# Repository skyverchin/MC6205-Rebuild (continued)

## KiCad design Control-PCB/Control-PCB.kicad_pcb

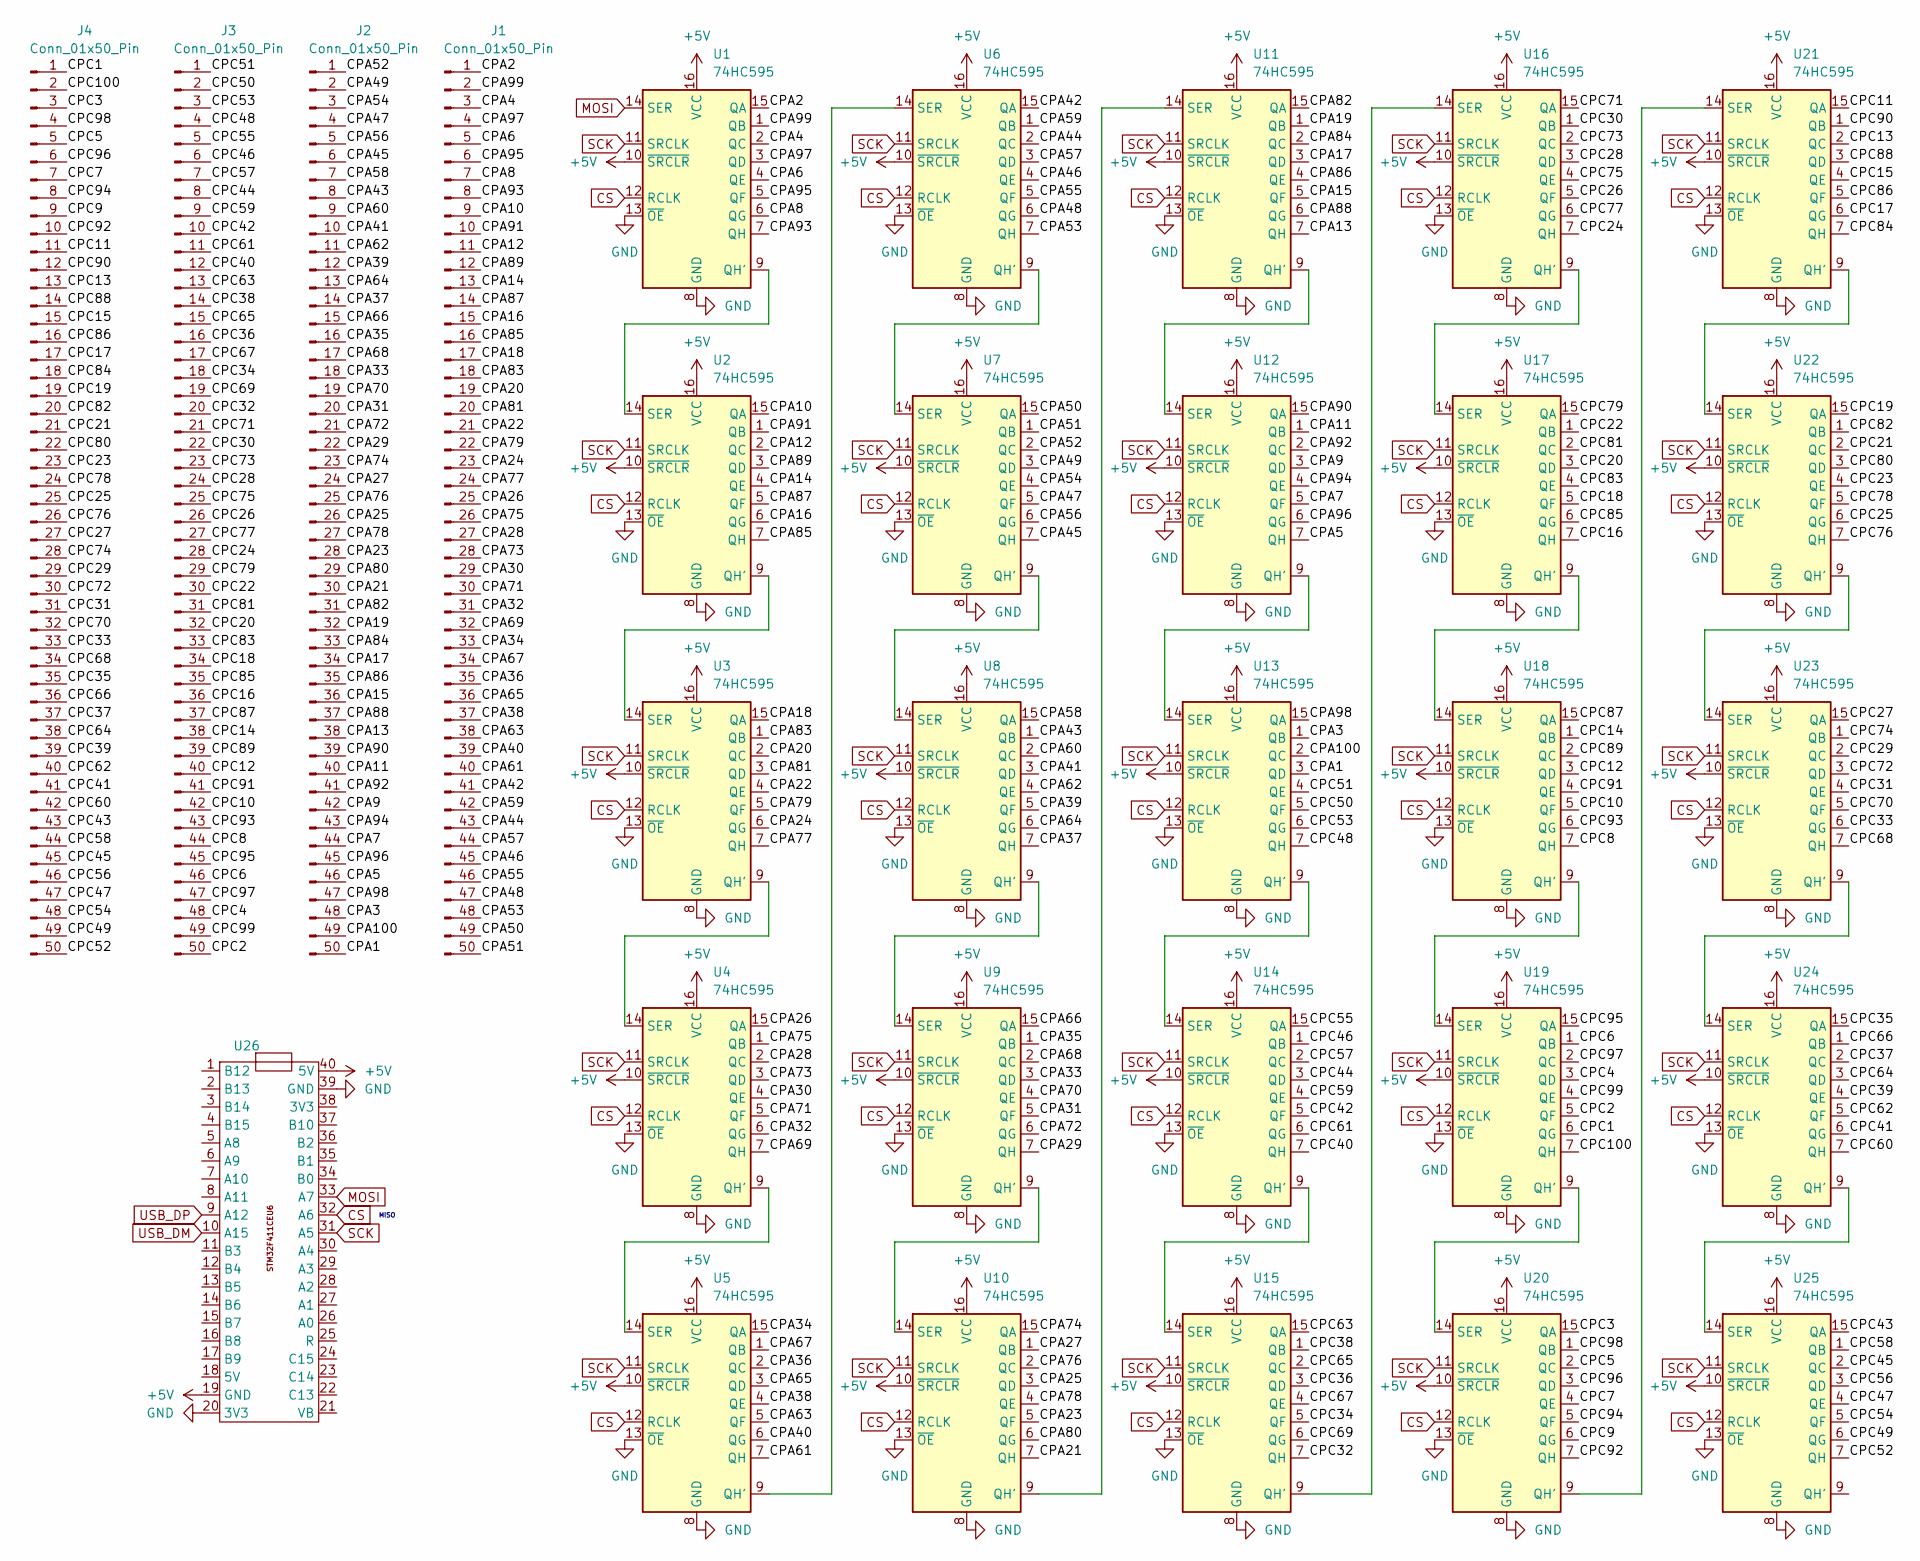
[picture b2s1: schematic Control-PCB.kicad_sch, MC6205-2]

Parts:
J1, J2, J3, J4: Conn_01x50_Pin; Molex_54132-5033_1x50-1MP_P0.5mm_Horizontal
U1, U2, U3, U4, U5, U6, U7, U8, U9, U10, U11, U12, U13, U14, U15, U16, U17, U18, U19, U20, U21, U22, U23, U24, U25: 74HC595; CERDIP-16_W7.62mm_SideBrazed
U26: DIP-40_W15.24mm

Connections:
+5V: U1.10 (~SRCLR), U1.16 (VCC), U2.10 (~SRCLR), U2.16 (VCC), U3.10 (~SRCLR), U3.16 (VCC), U4.10 (~SRCLR), U4.16 (VCC), U5.10 (~SRCLR), U5.16 (VCC), U6.10 (~SRCLR), U6.16 (VCC), U7.10 (~SRCLR), U7.16 (VCC), U8.10 (~SRCLR), U8.16 (VCC), U9.10 (~SRCLR), U9.16 (VCC), U10.10 (~SRCLR), U10.16 (VCC), U11.10 (~SRCLR), U11.16 (VCC), U12.10 (~SRCLR), U12.16 (VCC), U13.10 (~SRCLR), U13.16 (VCC), U14.10 (~SRCLR), U14.16 (VCC), U15.10 (~SRCLR), U15.16 (VCC), U16.10 (~SRCLR), U16.16 (VCC), U17.10 (~SRCLR), U17.16 (VCC), U18.10 (~SRCLR), U18.16 (VCC), U19.10 (~SRCLR), U19.16 (VCC), U20.10 (~SRCLR), U20.16 (VCC), U21.10 (~SRCLR), U21.16 (VCC), U22.10 (~SRCLR), U22.16 (VCC), U23.10 (~SRCLR), U23.16 (VCC), U24.10 (~SRCLR), U24.16 (VCC), U25.10 (~SRCLR), U25.16 (VCC), U26.19 (GND), U26.40 (5V)
/CPA1: J2.50, U13.3 (QD)
/CPA2: J1.1, U1.15 (QA)
/CPA3: J2.48, U13.1 (QB)
/CPA4: J1.3, U1.2 (QC)
/CPA5: J2.46, U12.7 (QH)
/CPA6: J1.5, U1.4 (QE)
/CPA7: J2.44, U12.5 (QF)
/CPA8: J1.7, U1.6 (QG)
/CPA9: J2.42, U12.3 (QD)
/CPA10: J1.9, U2.15 (QA)
/CPA11: J2.40, U12.1 (QB)
/CPA12: J1.11, U2.2 (QC)
/CPA13: J2.38, U11.7 (QH)
/CPA14: J1.13, U2.4 (QE)
/CPA15: J2.36, U11.5 (QF)
/CPA16: J1.15, U2.6 (QG)
/CPA17: J2.34, U11.3 (QD)
/CPA18: J1.17, U3.15 (QA)
/CPA19: J2.32, U11.1 (QB)
/CPA20: J1.19, U3.2 (QC)
/CPA21: J2.30, U10.7 (QH)
/CPA22: J1.21, U3.4 (QE)
/CPA23: J2.28, U10.5 (QF)
/CPA24: J1.23, U3.6 (QG)
/CPA25: J2.26, U10.3 (QD)
/CPA26: J1.25, U4.15 (QA)
/CPA27: J2.24, U10.1 (QB)
/CPA28: J1.27, U4.2 (QC)
/CPA29: J2.22, U9.7 (QH)
/CPA30: J1.29, U4.4 (QE)
/CPA31: J2.20, U9.5 (QF)
/CPA32: J1.31, U4.6 (QG)
/CPA33: J2.18, U9.3 (QD)
/CPA34: J1.33, U5.15 (QA)
/CPA35: J2.16, U9.1 (QB)
/CPA36: J1.35, U5.2 (QC)
/CPA37: J2.14, U8.7 (QH)
/CPA38: J1.37, U5.4 (QE)
/CPA39: J2.12, U8.5 (QF)
/CPA40: J1.39, U5.6 (QG)
/CPA41: J2.10, U8.3 (QD)
/CPA42: J1.41, U6.15 (QA)
/CPA43: J2.8, U8.1 (QB)
/CPA44: J1.43, U6.2 (QC)
/CPA45: J2.6, U7.7 (QH)
/CPA46: J1.45, U6.4 (QE)
/CPA47: J2.4, U7.5 (QF)
/CPA48: J1.47, U6.6 (QG)
/CPA49: J2.2, U7.3 (QD)
/CPA50: J1.49, U7.15 (QA)
/CPA51: J1.50, U7.1 (QB)
/CPA52: J2.1, U7.2 (QC)
/CPA53: J1.48, U6.7 (QH)
/CPA54: J2.3, U7.4 (QE)
/CPA55: J1.46, U6.5 (QF)
/CPA56: J2.5, U7.6 (QG)
/CPA57: J1.44, U6.3 (QD)
/CPA58: J2.7, U8.15 (QA)
/CPA59: J1.42, U6.1 (QB)
/CPA60: J2.9, U8.2 (QC)
/CPA61: J1.40, U5.7 (QH)
/CPA62: J2.11, U8.4 (QE)
/CPA63: J1.38, U5.5 (QF)
/CPA64: J2.13, U8.6 (QG)
/CPA65: J1.36, U5.3 (QD)
/CPA66: J2.15, U9.15 (QA)
/CPA67: J1.34, U5.1 (QB)
/CPA68: J2.17, U9.2 (QC)
/CPA69: J1.32, U4.7 (QH)
/CPA70: J2.19, U9.4 (QE)
/CPA71: J1.30, U4.5 (QF)
/CPA72: J2.21, U9.6 (QG)
/CPA73: J1.28, U4.3 (QD)
/CPA74: J2.23, U10.15 (QA)
/CPA75: J1.26, U4.1 (QB)
/CPA76: J2.25, U10.2 (QC)
/CPA77: J1.24, U3.7 (QH)
/CPA78: J2.27, U10.4 (QE)
/CPA79: J1.22, U3.5 (QF)
/CPA80: J2.29, U10.6 (QG)
/CPA81: J1.20, U3.3 (QD)
/CPA82: J2.31, U11.15 (QA)
/CPA83: J1.18, U3.1 (QB)
/CPA84: J2.33, U11.2 (QC)
/CPA85: J1.16, U2.7 (QH)
/CPA86: J2.35, U11.4 (QE)
/CPA87: J1.14, U2.5 (QF)
/CPA88: J2.37, U11.6 (QG)
/CPA89: J1.12, U2.3 (QD)
/CPA90: J2.39, U12.15 (QA)
/CPA91: J1.10, U2.1 (QB)
/CPA92: J2.41, U12.2 (QC)
/CPA93: J1.8, U1.7 (QH)
/CPA94: J2.43, U12.4 (QE)
/CPA95: J1.6, U1.5 (QF)
/CPA96: J2.45, U12.6 (QG)
/CPA97: J1.4, U1.3 (QD)
/CPA98: J2.47, U13.15 (QA)
/CPA99: J1.2, U1.1 (QB)
/CPA100: J2.49, U13.2 (QC)
/CPC1: J4.1, U19.6 (QG)
/CPC2: J3.50, U19.5 (QF)
/CPC3: J4.3, U20.15 (QA)
/CPC4: J3.48, U19.3 (QD)
/CPC5: J4.5, U20.2 (QC)
/CPC6: J3.46, U19.1 (QB)
/CPC7: J4.7, U20.4 (QE)
/CPC8: J3.44, U18.7 (QH)
/CPC9: J4.9, U20.6 (QG)
/CPC10: J3.42, U18.5 (QF)
/CPC11: J4.11, U21.15 (QA)
/CPC12: J3.40, U18.3 (QD)
/CPC13: J4.13, U21.2 (QC)
/CPC14: J3.38, U18.1 (QB)
/CPC15: J4.15, U21.4 (QE)
/CPC16: J3.36, U17.7 (QH)
/CPC17: J4.17, U21.6 (QG)
/CPC18: J3.34, U17.5 (QF)
/CPC19: J4.19, U22.15 (QA)
/CPC20: J3.32, U17.3 (QD)
/CPC21: J4.21, U22.2 (QC)
/CPC22: J3.30, U17.1 (QB)
/CPC23: J4.23, U22.4 (QE)
/CPC24: J3.28, U16.7 (QH)
/CPC25: J4.25, U22.6 (QG)
/CPC26: J3.26, U16.5 (QF)
/CPC27: J4.27, U23.15 (QA)
/CPC28: J3.24, U16.3 (QD)
/CPC29: J4.29, U23.2 (QC)
/CPC30: J3.22, U16.1 (QB)
/CPC31: J4.31, U23.4 (QE)
/CPC32: J3.20, U15.7 (QH)
/CPC33: J4.33, U23.6 (QG)
/CPC34: J3.18, U15.5 (QF)
/CPC35: J4.35, U24.15 (QA)
/CPC36: J3.16, U15.3 (QD)
/CPC37: J4.37, U24.2 (QC)
/CPC38: J3.14, U15.1 (QB)
/CPC39: J4.39, U24.4 (QE)
/CPC40: J3.12, U14.7 (QH)
/CPC41: J4.41, U24.6 (QG)
/CPC42: J3.10, U14.5 (QF)
/CPC43: J4.43, U25.15 (QA)
/CPC44: J3.8, U14.3 (QD)
/CPC45: J4.45, U25.2 (QC)
/CPC46: J3.6, U14.1 (QB)
/CPC47: J4.47, U25.4 (QE)
/CPC48: J3.4, U13.7 (QH)
/CPC49: J4.49, U25.6 (QG)
/CPC50: J3.2, U13.5 (QF)
/CPC51: J3.1, U13.4 (QE)
/CPC52: J4.50, U25.7 (QH)
/CPC53: J3.3, U13.6 (QG)
/CPC54: J4.48, U25.5 (QF)
/CPC55: J3.5, U14.15 (QA)
/CPC56: J4.46, U25.3 (QD)
/CPC57: J3.7, U14.2 (QC)
/CPC58: J4.44, U25.1 (QB)
/CPC59: J3.9, U14.4 (QE)
/CPC60: J4.42, U24.7 (QH)
/CPC61: J3.11, U14.6 (QG)
/CPC62: J4.40, U24.5 (QF)
/CPC63: J3.13, U15.15 (QA)
/CPC64: J4.38, U24.3 (QD)
/CPC65: J3.15, U15.2 (QC)
/CPC66: J4.36, U24.1 (QB)
/CPC67: J3.17, U15.4 (QE)
/CPC68: J4.34, U23.7 (QH)
/CPC69: J3.19, U15.6 (QG)
/CPC70: J4.32, U23.5 (QF)
/CPC71: J3.21, U16.15 (QA)
/CPC72: J4.30, U23.3 (QD)
/CPC73: J3.23, U16.2 (QC)
/CPC74: J4.28, U23.1 (QB)
/CPC75: J3.25, U16.4 (QE)
/CPC76: J4.26, U22.7 (QH)
/CPC77: J3.27, U16.6 (QG)
/CPC78: J4.24, U22.5 (QF)
/CPC79: J3.29, U17.15 (QA)
/CPC80: J4.22, U22.3 (QD)
/CPC81: J3.31, U17.2 (QC)
/CPC82: J4.20, U22.1 (QB)
/CPC83: J3.33, U17.4 (QE)
/CPC84: J4.18, U21.7 (QH)
/CPC85: J3.35, U17.6 (QG)
/CPC86: J4.16, U21.5 (QF)
/CPC87: J3.37, U18.15 (QA)
/CPC88: J4.14, U21.3 (QD)
/CPC89: J3.39, U18.2 (QC)
/CPC90: J4.12, U21.1 (QB)
/CPC91: J3.41, U18.4 (QE)
/CPC92: J4.10, U20.7 (QH)
/CPC93: J3.43, U18.6 (QG)
/CPC94: J4.8, U20.5 (QF)
/CPC95: J3.45, U19.15 (QA)
/CPC96: J4.6, U20.3 (QD)
/CPC97: J3.47, U19.2 (QC)
/CPC98: J4.4, U20.1 (QB)
/CPC99: J3.49, U19.4 (QE)
/CPC100: J4.2, U19.7 (QH)
CS: U1.12 (RCLK), U2.12 (RCLK), U3.12 (RCLK), U4.12 (RCLK), U5.12 (RCLK), U6.12 (RCLK), U7.12 (RCLK), U8.12 (RCLK), U9.12 (RCLK), U10.12 (RCLK), U11.12 (RCLK), U12.12 (RCLK), U13.12 (RCLK), U14.12 (RCLK), U15.12 (RCLK), U16.12 (RCLK), U17.12 (RCLK), U18.12 (RCLK), U19.12 (RCLK), U20.12 (RCLK), U21.12 (RCLK), U22.12 (RCLK), U23.12 (RCLK), U24.12 (RCLK), U25.12 (RCLK), U26.32 (A6)
GND: U1.8 (GND), U1.13 (~OE), U2.8 (GND), U2.13 (~OE), U3.8 (GND), U3.13 (~OE), U4.8 (GND), U4.13 (~OE), U5.8 (GND), U5.13 (~OE), U6.8 (GND), U6.13 (~OE), U7.8 (GND), U7.13 (~OE), U8.8 (GND), U8.13 (~OE), U9.8 (GND), U9.13 (~OE), U10.8 (GND), U10.13 (~OE), U11.8 (GND), U11.13 (~OE), U12.8 (GND), U12.13 (~OE), U13.8 (GND), U13.13 (~OE), U14.8 (GND), U14.13 (~OE), U15.8 (GND), U15.13 (~OE), U16.8 (GND), U16.13 (~OE), U17.8 (GND), U17.13 (~OE), U18.8 (GND), U18.13 (~OE), U19.8 (GND), U19.13 (~OE), U20.8 (GND), U20.13 (~OE), U21.8 (GND), U21.13 (~OE), U22.8 (GND), U22.13 (~OE), U23.8 (GND), U23.13 (~OE), U24.8 (GND), U24.13 (~OE), U25.8 (GND), U25.13 (~OE), U26.20 (3V3), U26.39 (GND)
MOSI: U1.14 (SER), U26.33 (A7)
unnamed: U1.9 (QH'), U2.14 (SER)
unnamed: U2.9 (QH'), U3.14 (SER)
unnamed: U3.9 (QH'), U4.14 (SER)
unnamed: U4.9 (QH'), U5.14 (SER)
unnamed: U5.9 (QH'), U6.14 (SER)
unnamed: U6.9 (QH'), U7.14 (SER)
unnamed: U7.9 (QH'), U8.14 (SER)
unnamed: U8.9 (QH'), U9.14 (SER)
unnamed: U10.9 (QH'), U11.14 (SER)
unnamed: U9.9 (QH'), U10.14 (SER)
unnamed: U11.9 (QH'), U12.14 (SER)
unnamed: U12.9 (QH'), U13.14 (SER)
unnamed: U13.9 (QH'), U14.14 (SER)
unnamed: U14.9 (QH'), U15.14 (SER)
unnamed: U15.9 (QH'), U16.14 (SER)
unnamed: U16.9 (QH'), U17.14 (SER)
unnamed: U17.9 (QH'), U18.14 (SER)
unnamed: U18.9 (QH'), U19.14 (SER)
unnamed: U19.9 (QH'), U20.14 (SER)
unnamed: U20.9 (QH'), U21.14 (SER)
unnamed: U21.9 (QH'), U22.14 (SER)
unnamed: U22.9 (QH'), U23.14 (SER)
unnamed: U23.9 (QH'), U24.14 (SER)
unnamed: U24.9 (QH'), U25.14 (SER)
SCK: U1.11 (SRCLK), U2.11 (SRCLK), U3.11 (SRCLK), U4.11 (SRCLK), U5.11 (SRCLK), U6.11 (SRCLK), U7.11 (SRCLK), U8.11 (SRCLK), U9.11 (SRCLK), U10.11 (SRCLK), U11.11 (SRCLK), U12.11 (SRCLK), U13.11 (SRCLK), U14.11 (SRCLK), U15.11 (SRCLK), U16.11 (SRCLK), U17.11 (SRCLK), U18.11 (SRCLK), U19.11 (SRCLK), U20.11 (SRCLK), U21.11 (SRCLK), U22.11 (SRCLK), U23.11 (SRCLK), U24.11 (SRCLK), U25.11 (SRCLK), U26.31 (A5)
USB_DM: U26.10 (A15)
USB_DP: U26.9 (A12)

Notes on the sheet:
MISO

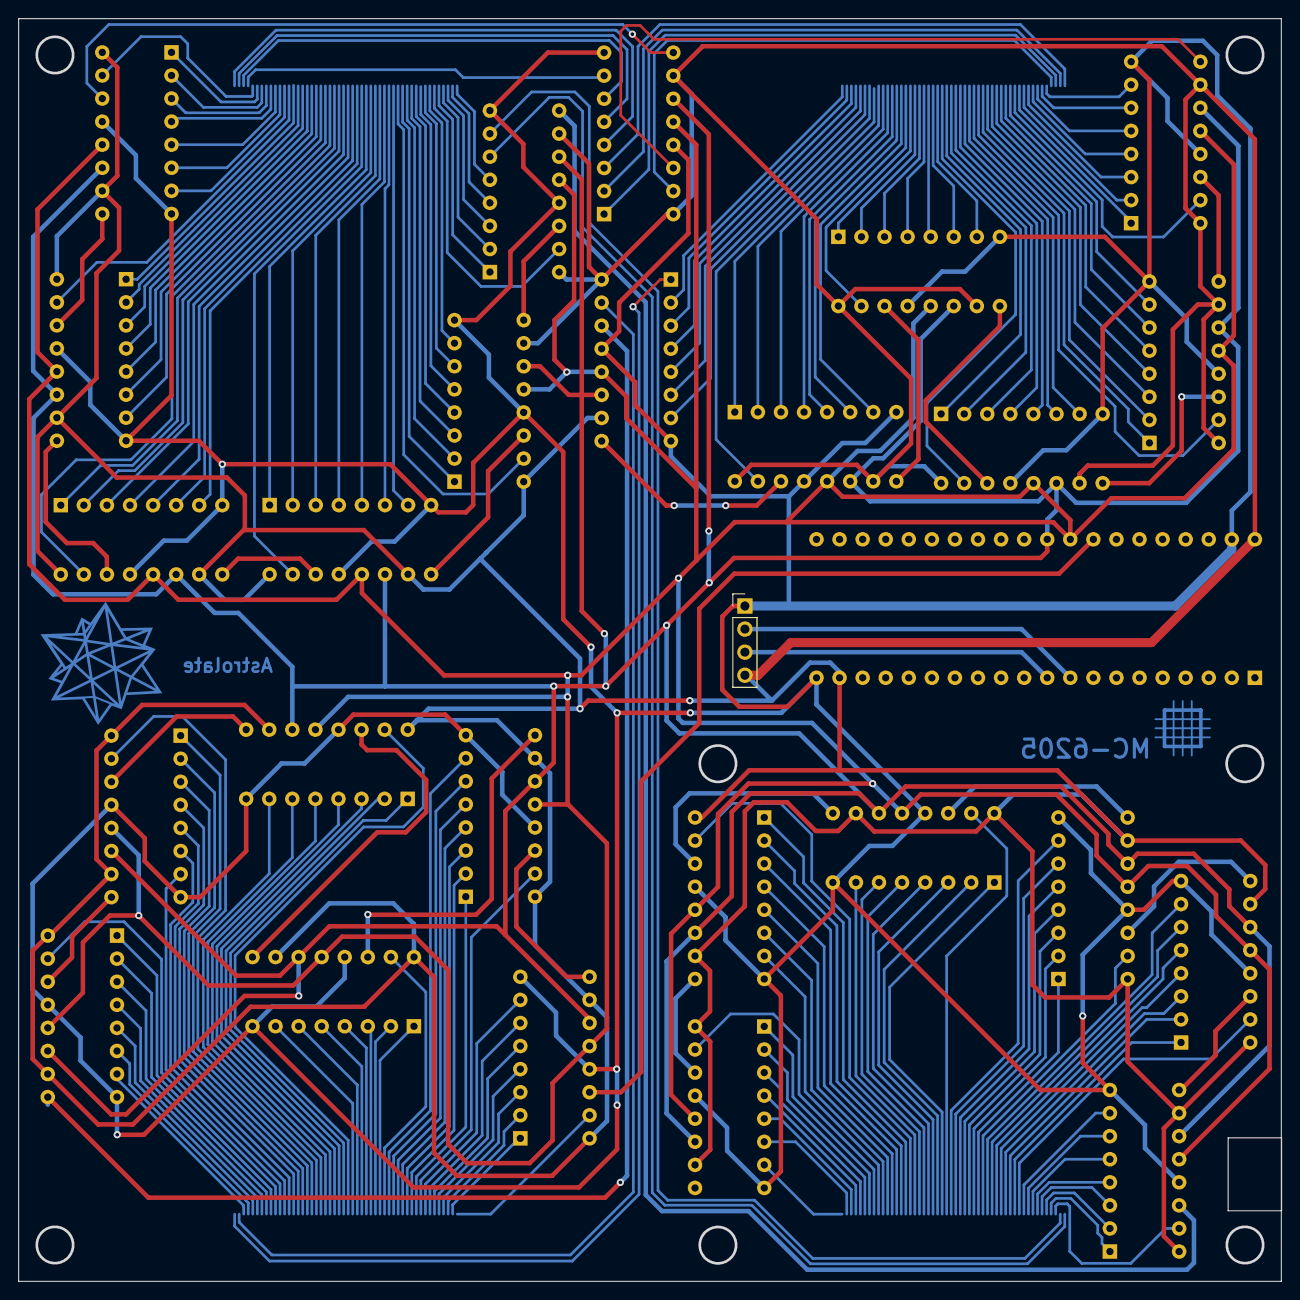
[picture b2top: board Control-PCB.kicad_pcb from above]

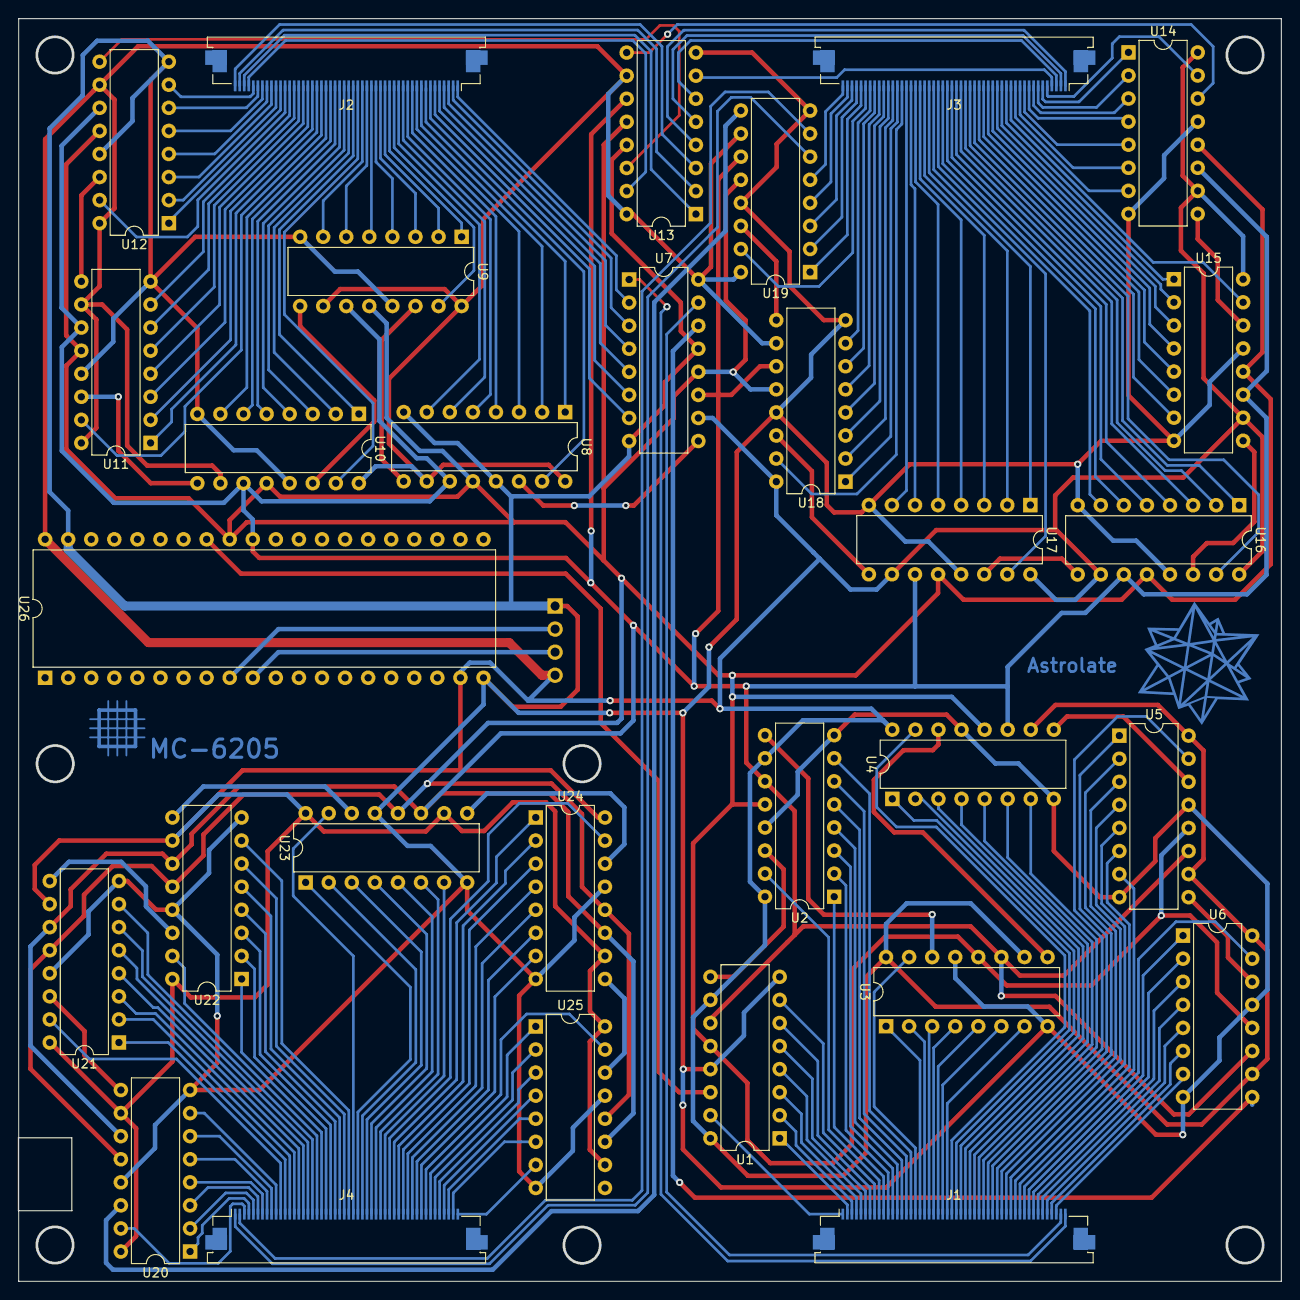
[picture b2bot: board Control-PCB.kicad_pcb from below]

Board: 2 copper layers, 139.0 x 139.0 mm, 30 parts (30 on the bottom side), 229 nets.

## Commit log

2024-06-14 Add basics files
2024-06-14 test
2024-06-14 Rolling Back Changes
2024-06-23 add footprints
2024-10-20 pcb and docs
2024-10-20 new images
2025-01-16 pcb updates
2025-01-16 minor changes
